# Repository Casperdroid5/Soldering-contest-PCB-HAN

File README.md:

# Soldering Contest PCB (HAN)

The PCB has been created specifically for the soldering contest. It is designed to help students in the ESE course develop their soldering skills for both surface-mount (SMD) and through-hole (THT) components of different sizes.

## Key Features

- **Component Variety:** The PCB includes a diverse range of SMD and THT components of different sizes and types. This allows students to practice soldering techniques for various components.

- **Component Footprints:** Different component footprints are included on the PCB to accommodate various package types such as resistors, capacitors, diodes, ICs, and connectors. This exposes students to different soldering techniques required for each component type.

- **Test Points:** The PCB features strategically placed test points that enable instructors to measure the quality of solder joints. These test points assess students' soldering technique and the electrical connectivity of the components.

- **Thermal Pads:** Components with thermal pads are incorporated to test students' ability to handle heat dissipation during soldering. This provides experience in soldering components that require special attention to avoid overheating or cold solder joints.

- **Solder Mask Openings:** Small solder mask openings are introduced on some pads to assess students' precision and control during soldering. This challenges them to avoid bridging adjacent pads or leaving solder residues on the mask.

- **Multiple Soldering Techniques:** The PCB is designed to encourage the use of different soldering techniques. It includes components that require drag soldering, reflow soldering, or hand-soldering under a microscope. This helps students become proficient in a variety of soldering methods.

- **Soldering Station Settings:** Clear guidelines or recommendations for soldering station settings are provided, including temperature, soldering iron tip selection, and solder types suitable for the components on the PCB. This helps students understand the importance of proper soldering equipment setup for different scenarios.

- **Grading Criteria:** A grading rubric is defined, covering soldering technique, joint appearance, component alignment, cleanliness, and electrical continuity. This ensures students understand how their work will be evaluated.

- **Documentation and Resources:** Documentation or resources such as a soldering guide or reference materials are provided for students to refer to during the contest. This helps familiarize them with best practices and techniques before starting their soldering tasks.

- **Safety Considerations:** Emphasis is placed on safety precautions during soldering, including proper ventilation, eye protection, and safe handling of soldering equipment. The contest follows appropriate safety protocols to protect the students and instructors.

## Soldering Tips and Advice

Soldering is a delicate process that requires skill, precision, and attention to detail. Here are some helpful tips and advice to assist students participating in the soldering contest:

1. **Prepare your workspace:** Ensure you have a clean and well-organized workspace. Remove any unnecessary clutter, and have all your tools and components easily accessible. A clutter-free area allows you to focus on the soldering task at hand and reduces the chances of accidental damage or mistakes.

2. **Inspect the PCB and components:** Before starting, carefully inspect the PCB and components for any defects or damage. Check for bent pins, damaged traces, or missing components. Address any issues before proceeding with soldering to avoid complications later.

3. **Choose the right soldering iron tip:** Select an appropriate soldering iron tip based on the component size and type. A fine-point tip works well for small SMD components, while a chisel or screwdriver tip is suitable for larger THT components. Ensure the tip is clean and properly tinned for optimal heat transfer.

4. **Maintain proper temperature:** Set the soldering iron temperature according to the solder and component requirements. Too high a temperature can damage components or lead to overheating, while too low a temperature can result in cold solder joints. Follow the recommended temperature range provided for the contest.

5. **Cleanliness is crucial:** Keep your soldering iron tip clean by regularly wiping it on a damp sponge or brass tip cleaner. This helps remove oxidation and ensures good heat transfer. Additionally, keep the components, PCB, and soldering area clean from flux residues or excess solder. Use flux remover or isopropyl alcohol for cleaning, if necessary.

6. **Practice good soldering technique:** Master the art of soldering by practicing proper technique. Hold the soldering iron like a pen, with a light grip, and apply gentle pressure. Ensure the tip touches both the pad and the component lead simultaneously to allow efficient heat transfer. Feed a small amount of solder at the junction, and let it flow smoothly.

7. **Avoid excessive heat:** Minimize the time the soldering iron spends in contact with the component leads or pads to prevent overheating. Prolonged exposure to heat can damage sensitive components or surrounding parts. Develop a steady and controlled soldering rhythm to ensure quick, yet accurate, soldering.

8. **Prevent solder bridges:** Take care to avoid solder bridges, which occur when solder connects adjacent pads or pins. Use a magnifying glass or a microscope to closely inspect your work, especially when soldering small, closely spaced components. If solder bridges occur, use desoldering braid or a solder sucker to remove excess solder.

9. **Ensure proper joint formation:** Aim for shiny, concave solder joints that indicate a proper bond. Dull or irregular joints may indicate cold solder joints or insufficient solder. If needed, reheat the joint and add a small amount of solder to achieve a well-formed, reliable connection.

10. **Test continuity and functionality:** Once soldering is complete, use a multimeter or other appropriate testing methods to check the electrical continuity and functionality of the soldered components. This ensures that the connections are secure and the circuit operates as intended.

Remember, soldering is a skill that improves with practice. Take your time, be patient, and learn from each soldering experience. Don't hesitate to ask for guidance or clarification if you have any doubts. Enjoy the soldering process and have confidence in your abilities!

*Note: The soldering tips and advice provided here are general guidelines. Always refer to the specific instructions, safety precautions, and grading criteria provided by the contest organizers for accurate information and requirements.*

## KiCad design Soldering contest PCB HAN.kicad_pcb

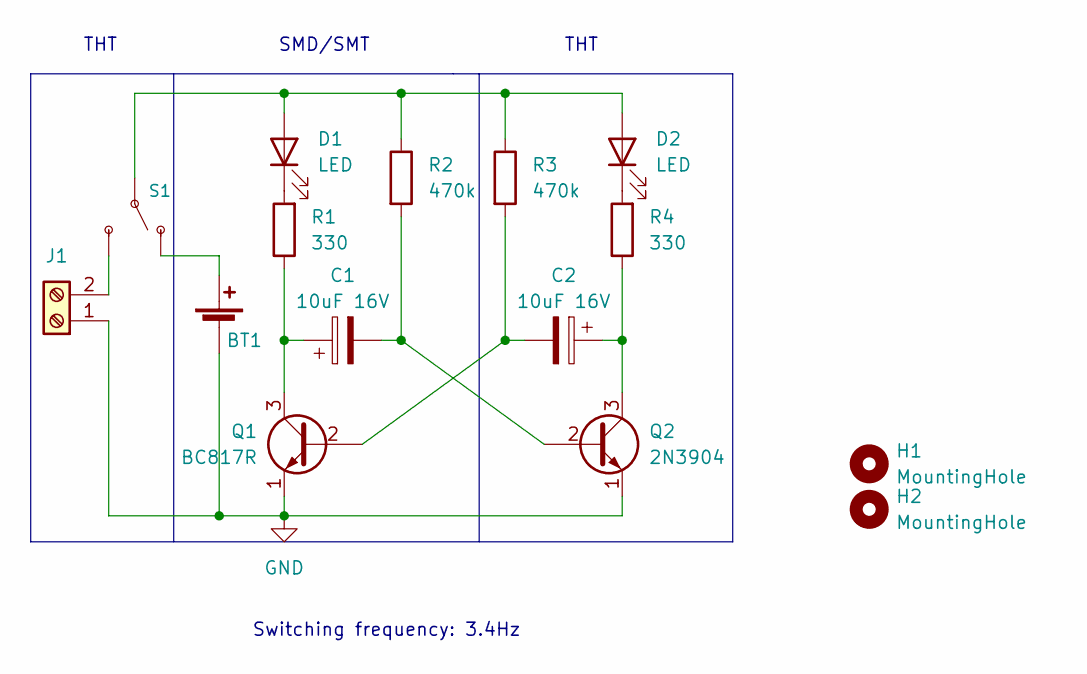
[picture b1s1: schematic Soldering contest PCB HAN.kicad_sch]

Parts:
BT1: Battery_Cell; BatteryHolder_Keystone_3002_1x2032
C1: 10uF 16V; C_1206_3216Metric_Pad1.33x1.80mm_HandSolder
C2: 10uF 16V; CP_Radial_D4.0mm_P2.00mm
D1: LED; LED_0805_2012Metric_Pad1.15x1.40mm_HandSolder
D2: LED; LED_D5.0mm_Clear
H1, H2: MountingHole; MountingHole_4.3mm_M4
J1: Screw_Terminal_01x02; TerminalBlock_bornier-2_P5.08mm
Q1: BC817R; SOT-23_Handsoldering
Q2: 2N3904; TO-92_Inline_Wide
R1: 330; R_0402_1005Metric
R2: 470k; R_0805_2012Metric_Pad1.20x1.40mm_HandSolder
R3: 470k; R_Axial_DIN0204_L3.6mm_D1.6mm_P2.54mm_Vertical
R4: 330; R_Axial_DIN0207_L6.3mm_D2.5mm_P7.62mm_Horizontal
S1: SWITCH-SPDT-PTH-11.6X4.0MM-KIT; SW_1825159-1

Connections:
GND: BT1.2 (-), J1.1, Q1.1 (E), Q2.1 (E)
unnamed: BT1.1 (+), S1.1 (O)
unnamed: C1.1, Q1.3 (C), R1.1
unnamed: C1.2, Q2.2 (B), R2.2
unnamed: C2.1, Q2.3 (C), R4.1
unnamed: C2.2, Q1.2 (B), R3.2
unnamed: D1.1 (K), R1.2
unnamed: D1.2 (A), D2.2 (A), R2.1, R3.1, S1.2
unnamed: D2.1 (K), R4.2
unnamed: J1.2, S1.3 (S)

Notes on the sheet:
SMD/SMT
THT
Switching frequency: 3.4Hz

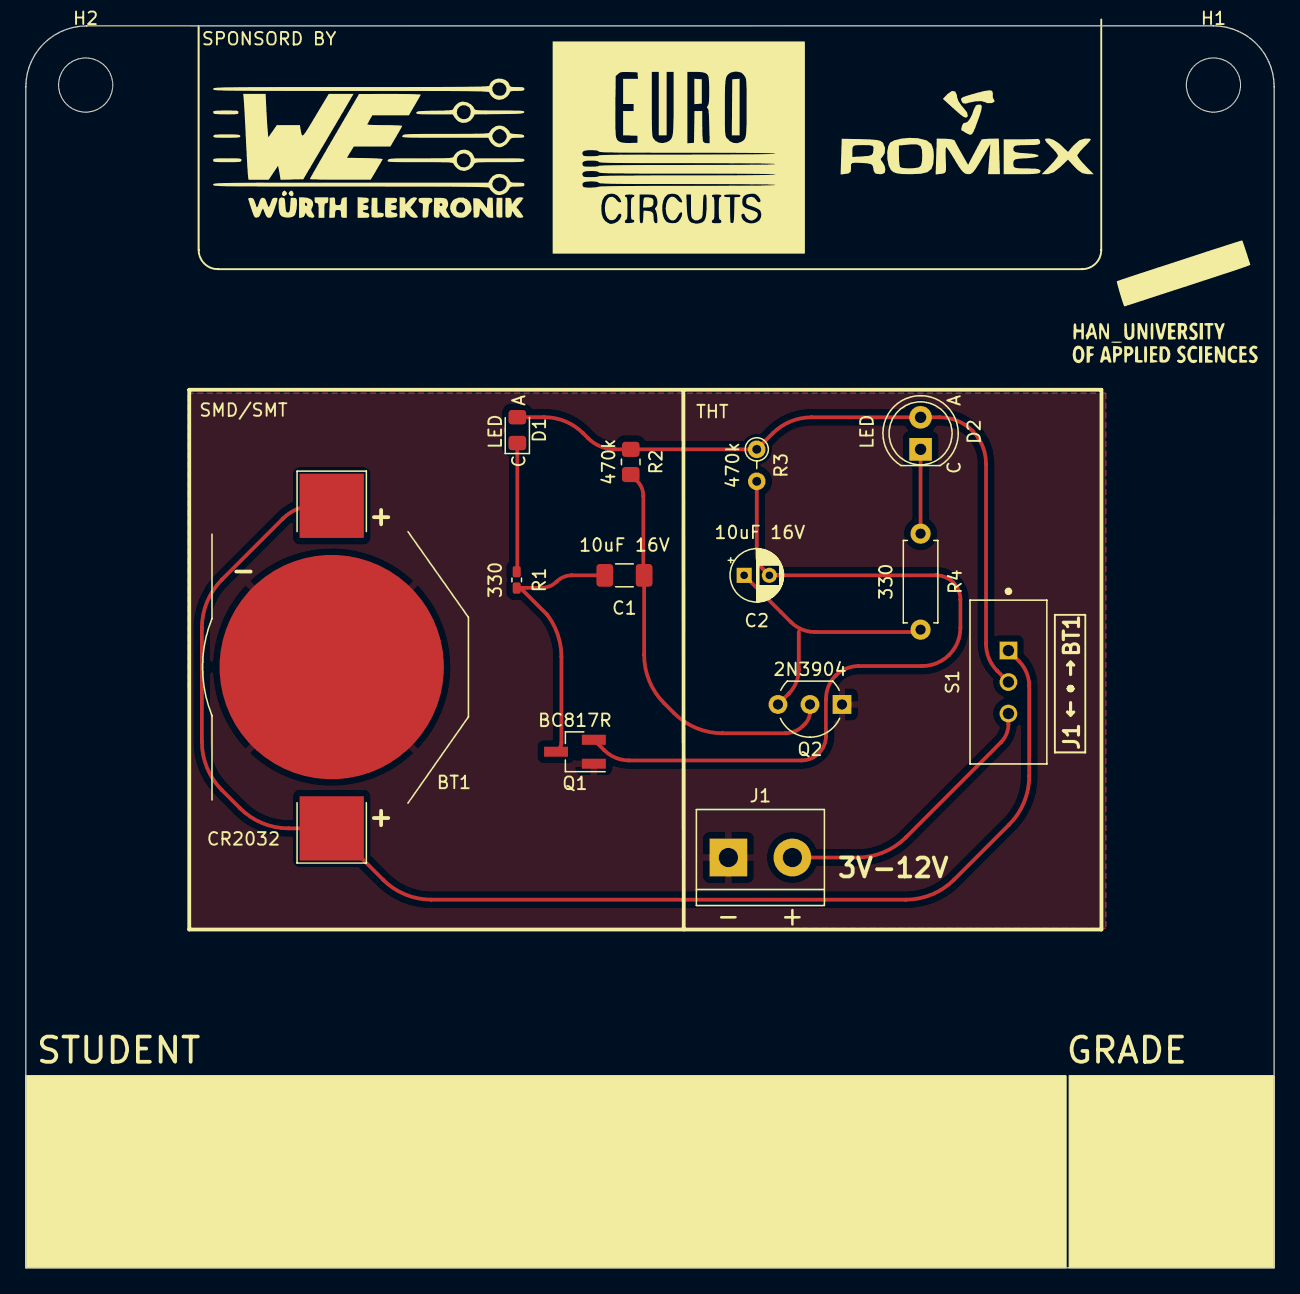
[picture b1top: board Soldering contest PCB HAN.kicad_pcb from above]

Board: 2 copper layers, 99.1 x 98.6 mm, 15 parts (0 on the bottom side), 10 nets.

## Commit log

2022-11-18 Initial commit
    added schematic with details on project
    added requirements file (empty)
2022-11-18 created requirements
    Inspired by the conversation with Remko Welling
2022-11-18 Schematic created
    Basic circuit has been drawn
2022-11-18 added values and references to components
    Some values may be tweaked later
2022-11-18 defined smd and tht sides of schematic
2022-11-18 assigned footprints
2022-11-18 Update README.md
    changed name to soldering
2022-11-18 improved schematic board size
2022-11-18 replaced q1 footprint
    replaced with sot23 handsolderable
2022-11-18 archived 3d model, created general layout
2022-11-18 changed Q2 footprint
    to to92 wide
2022-11-18 changed r3 footprint
    smaller, so it's clear that it has to be soldered vertically
2022-11-18 Wiring complete
2022-11-18 added ground plane
    for demonstration purposes
2022-11-18 added tips and sponsors to documentation
2022-11-18 cleanup 3d
2022-11-18 started on silkscreen
    added student and grade boxes
2022-11-18 rounded corners
2022-11-18 added tips and project name to backsilk
2022-11-18 improved silkscreen text and made it pretier
2022-11-18 finished pcb design V0.1
2022-11-18 changed terminal position
2022-11-18 incorporated Remko's feedback
    -added Romex logo
    -added text: "Designed for: ESE-day 27 January 2023 soldering contest"
    -moved terminal to mid bottom to balance weight
    -
2022-11-18 removed tips, added ESE txt
2022-11-18 added todo list
2022-11-21 add bat, switch changed schematic
2022-11-21 improved wiring and connected everything
2022-11-21 Working on ERC
2022-11-21 archived 3d models
2022-11-21 added component values to silkscreen
2022-11-21 Finished V0.2
    -added Remko's feedback
    -changed a few component names to their smd parts
    -added gitlab repo link to pcb (not yet uploaded to gitlab)
2022-11-21 cleanup
2022-11-21 git ignored improved
    ignore all backups
2022-11-21 added bom and schematic pdf
2022-11-21 improved values
2022-11-21 updated bom
2022-11-21 cleanup + new pdf
2022-11-21 Added the correct values to the components
    -R val
    -C val
2022-11-21 Finished V0.2
    -added interactive BOM
    -added improved schematic
2022-11-21 added rounded tracks version of V0.2
2022-11-22 small improvements on silkscreen
2022-11-28 enh board
    -added mounting holes
    -updated silkscreen date
    -changed R1 footprint to match ERC
2022-11-28 added Romex logo to doc file
2022-11-28 alligned center of pcb
2022-11-28 added new interactive bom
2022-11-28 added BOM
2022-11-28 final silkscreen improvements
2022-11-28 finalised V0.4
    -cleanup and recenterd
2022-11-28 updated pcb v0.4 file
2022-12-01 added kicad logo
2022-12-01 added kicad logo and updated version number
2023-01-26 Updated component
    BC817 -> BC817R
2023-05-24 Update README.md
    extension on soldering contest itself, and safety/tips
2023-12-30 added pictures of board
